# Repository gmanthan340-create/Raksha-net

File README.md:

# Raksha-net
A resilient disaster communication system using ESP32, LoRa mesh networking, GNSS and AI-based message prioritization (integration).

### Disaster Mesh Communication Network

A resilient emergency communication system designed to enable communication during disasters when conventional cellular and internet networks are unavailable.

---

##  Problem

During disasters such as floods, earthquakes, landslides and other emergencies, conventional communication infrastructure can become unavailable.

This can make it difficult for:

- Victims to send SOS messages
- Rescue teams to receive accurate locations
- Emergency information to reach command centers
- Rescue teams to coordinate effectively

---

##  Our Solution

**Raksha-Net** uses a decentralized LoRa-based mesh network to provide communication between field devices without depending on cellular networks or the internet.

##  Communication

Raksha-Net uses LoRa-based multi-hop communication to transmit emergency information across the mesh network.

Key concepts include:

- Multi-hop communication
- Store-and-forward messaging
- Self-healing mesh
- SOS prioritization
- Location sharing
- Route selection

# AI Integration

The AI layer is designed to assist the emergency communication system by:

Classifying emergency messages
Prioritizing SOS information
Assisting route selection
Considering factors such as signal strength, battery level and network conditions

The goal is to ensure that critical emergency information receives higher priority within the network.

# Hardware

The emergency node prototype consists of:

ESP32
LoRa communication module
GNSS/GPS module
SOS push button
SOS LED
Buzzer
Battery power system
3.3V voltage regulation
USB-C interface

# PCB Design

The PCB was designed using KiCad.

PCB 3D Model

The PCB integrates the controller, communication interfaces, emergency interface and power circuitry into a compact prototype.

## Smart India Hackathon 2026

Problem Statement: SIH26223
Domain: Hardware – Disaster Management

Team SIX MVPs
Manthan Gurav — Project Lead
Viraj Patil
Vaishnav Patil
Parul Sharma
Shreya Singh
Soham Nikam

## Project Status

The current PCB is a prototype design intended for demonstration and validation.

The exact commercially purchased components and footprints should be verified before manufacturing the final PCB.

## Project Demonstration

YouTube demonstration coming soon.

## License

This project is developed as part of Smart India Hackathon 2026.

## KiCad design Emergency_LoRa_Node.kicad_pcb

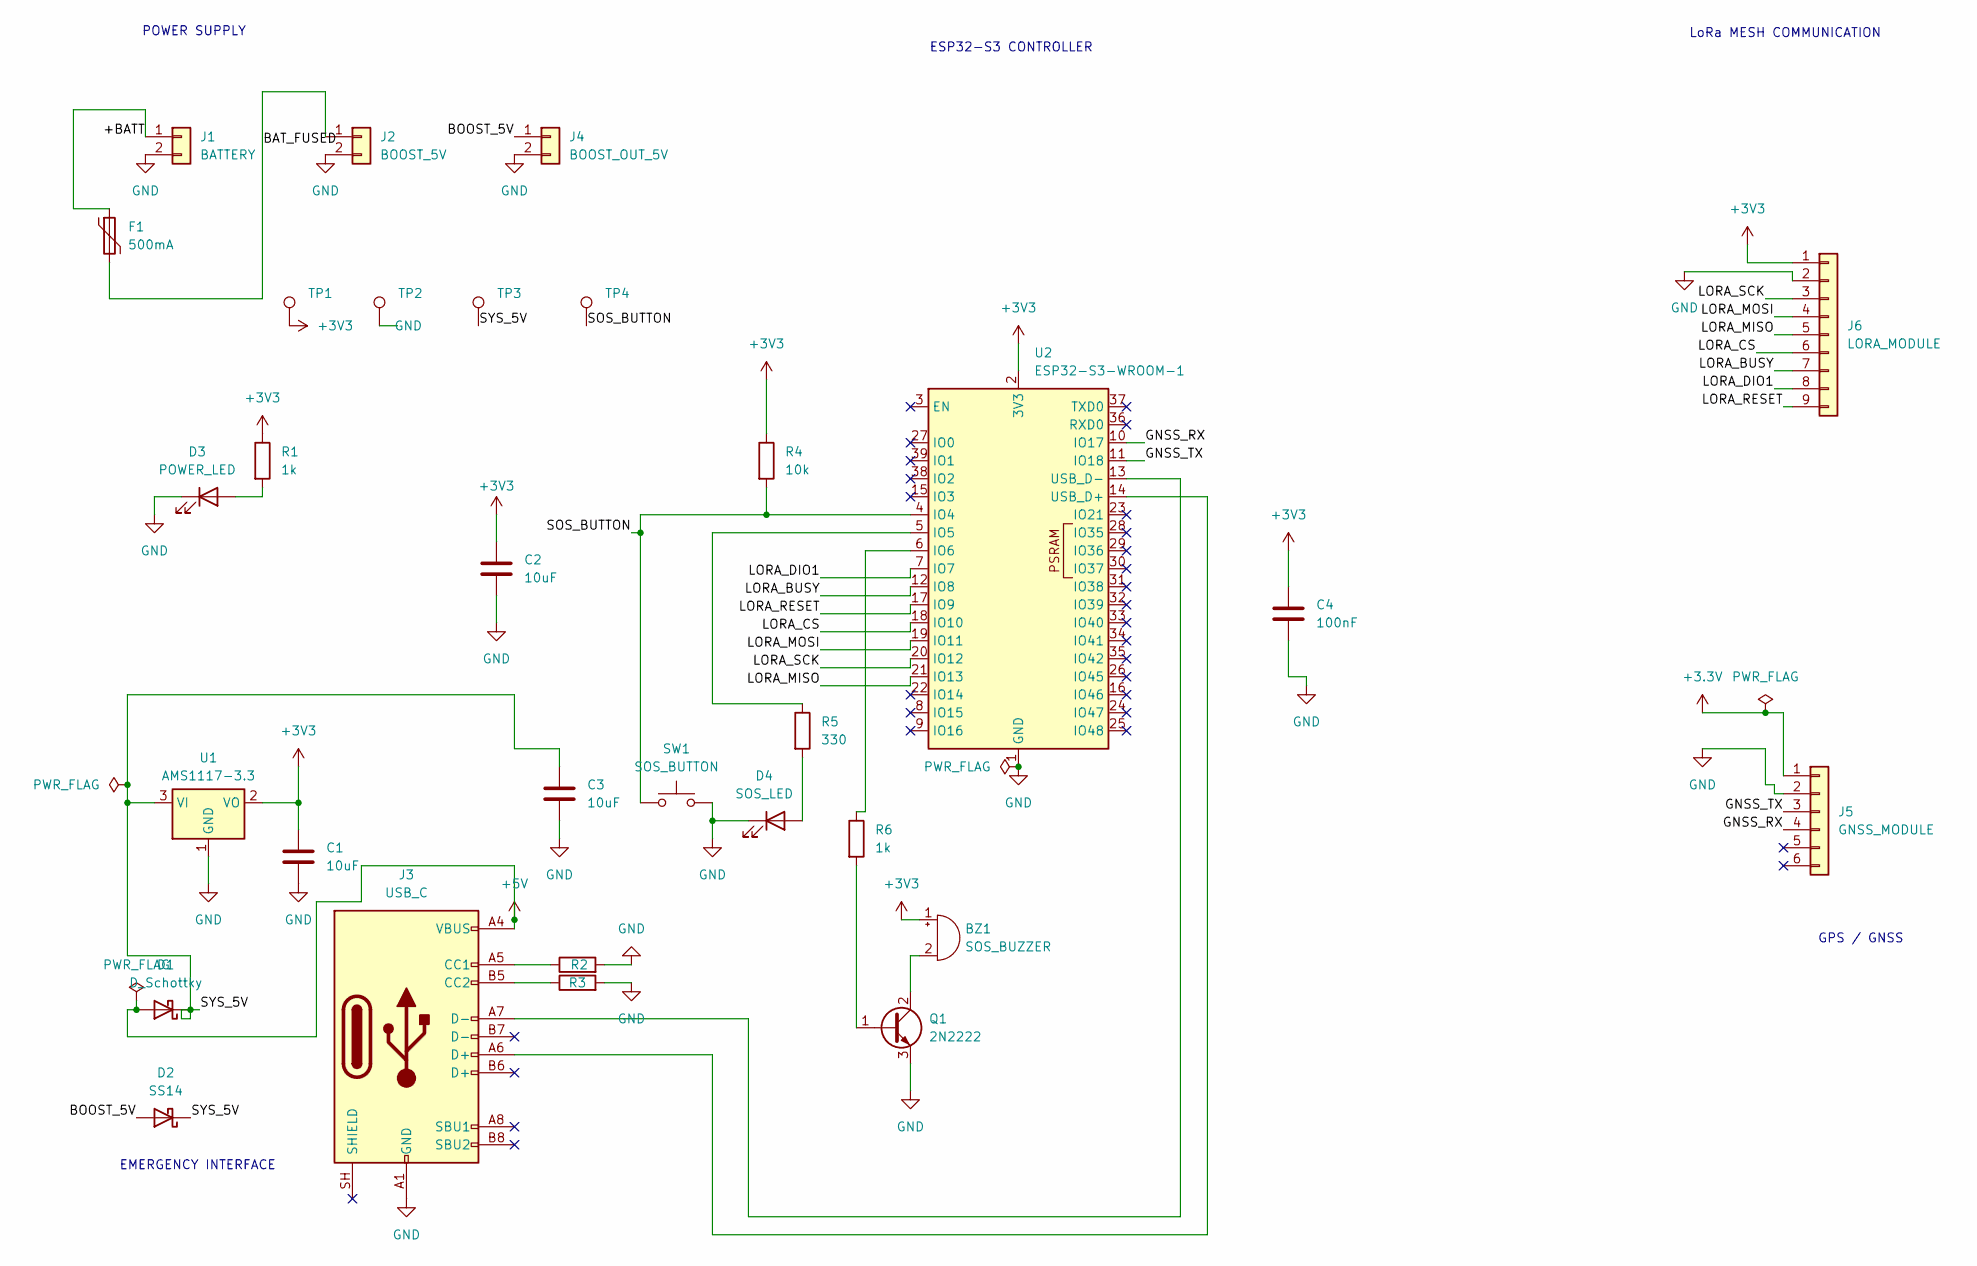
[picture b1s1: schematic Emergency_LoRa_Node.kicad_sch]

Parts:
BZ1: SOS_BUZZER; Buzzer_12x9.5RM7.6
C1, C2, C3: 10uF; C_0805_2012Metric
C4: 100nF; C_0805_2012Metric
D1: D_Schottky; D_SMA
D2: SS14; D_SMA
D3: POWER_LED; LED_0805_2012Metric
D4: SOS_LED; LED_0805_2012Metric
F1: 500mA; Fuse_1206_3216Metric
J1: BATTERY; PinHeader_1x02_P2.54mm_Vertical
J2: BOOST_5V; PinHeader_1x02_P2.54mm_Vertical
J3: USB_C; USB_C_Receptacle_GCT_USB4105-xx-A_16P_TopMnt_Horizontal
J4: BOOST_OUT_5V; PinHeader_1x02_P2.54mm_Vertical
J5: GNSS_MODULE; PinHeader_1x06_P2.54mm_Vertical
J6: LORA_MODULE; PinHeader_1x09_P2.54mm_Vertical
Q1: 2N2222; TO-92_Inline
R1, R6: 1k; R_0805_2012Metric
R2, R3: R; R_0805_2012Metric
R4: 10k; R_0805_2012Metric
R5: 330; R_0805_2012Metric
SW1: SOS_BUTTON; SW_PUSH_6mm
TP1: +3V3; TestPoint_Plated_Hole_D2.0mm
TP2: GND; TestPoint_Plated_Hole_D2.0mm
TP3, TP4: TestPoint; TestPoint_Plated_Hole_D2.0mm
U1: AMS1117-3.3; SOT-223-3_TabPin2
U2: ESP32-S3-WROOM-1; ESP32-S3-WROOM-1U

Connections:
+3.3V: J5.1
+3V3: BZ1.1 (+), C1.1, C2.1, C4.1, J6.1, R1.1, R4.1, TP1.1 (1_1), U1.2 (VO), U2.2 (3V3)
+5V: D1.2 (A), J3.A4 (VBUS), J3.A9 (VBUS), J3.B4 (VBUS), J3.B9 (VBUS), TP2.1 (1_1)
/+BATT: F1.1, J1.1
/BAT_FUSED: F1.2, J2.1
/BOOST_5V: D2.2 (A), J4.1
/GNSS_RX: J5.4, U2.10 (IO17)
/GNSS_TX: J5.3, U2.11 (IO18)
/LORA_BUSY: J6.7, U2.12 (IO8)
/LORA_CS: J6.6, U2.18 (IO10)
/LORA_DIO1: J6.8, U2.7 (IO7)
/LORA_MISO: J6.5, U2.21 (IO13)
/LORA_MOSI: J6.4, U2.19 (IO11)
/LORA_RESET: J6.9, U2.17 (IO9)
/LORA_SCK: J6.3, U2.20 (IO12)
/SOS_BUTTON: R4.2, SW1.1, TP4.1 (1_1), U2.4 (IO4)
/SYS_5V: C3.1, D1.1 (K), D2.1 (K), TP3.1 (1_1), U1.3 (VI)
GND: C1.2, C2.2, C3.2, C4.2, D3.1 (K), D4.1 (K), J1.2, J2.2, J3.A1 (GND), J3.A12 (GND), J3.B1 (GND), J3.B12 (GND), J4.2, J5.2, J6.2, Q1.3 (E), R2.2, R3.2, SW1.2, U1.1 (GND), U2.1 (GND), U2.40 (GND), U2.41 (GND)
unnamed: BZ1.2 (-), Q1.2 (C)
unnamed: D3.2 (A), R1.2
unnamed: D4.2 (A), R5.2
unnamed: J3.A5 (CC1), R2.1
unnamed: J3.B5 (CC2), R3.1
unnamed: Q1.1 (B), R6.2
unnamed: R5.1, U2.5 (IO5)
unnamed: R6.1, U2.6 (IO6)
unnamed: J3.A6 (D+), U2.14 (USB_D+)
unnamed: J3.A7 (D-), U2.13 (USB_D-)

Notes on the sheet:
LoRa MESH COMMUNICATION
ESP32-S3 CONTROLLER
GPS / GNSS
POWER SUPPLY
EMERGENCY INTERFACE

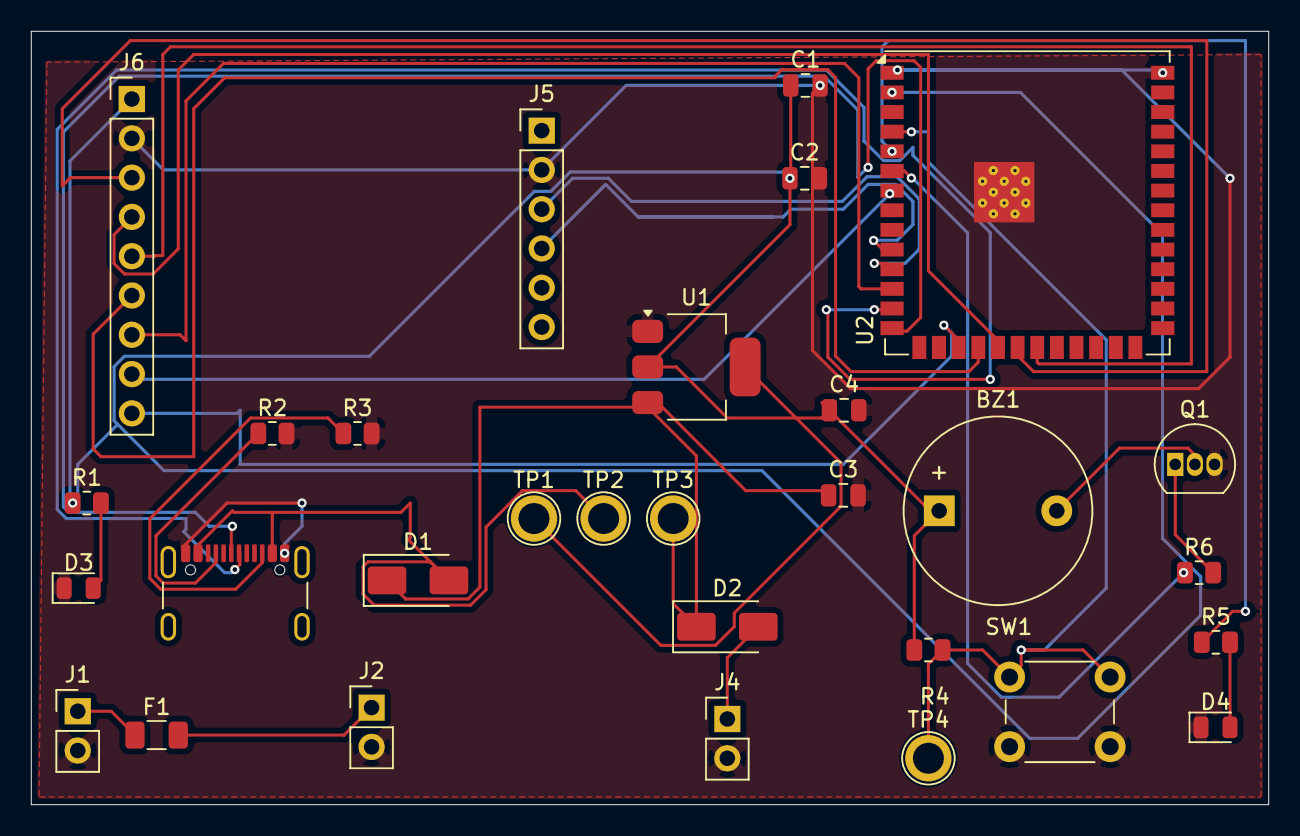
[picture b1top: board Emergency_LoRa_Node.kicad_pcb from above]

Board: 2 copper layers, 80.0 x 50.0 mm, 30 parts (0 on the bottom side), 27 nets.
